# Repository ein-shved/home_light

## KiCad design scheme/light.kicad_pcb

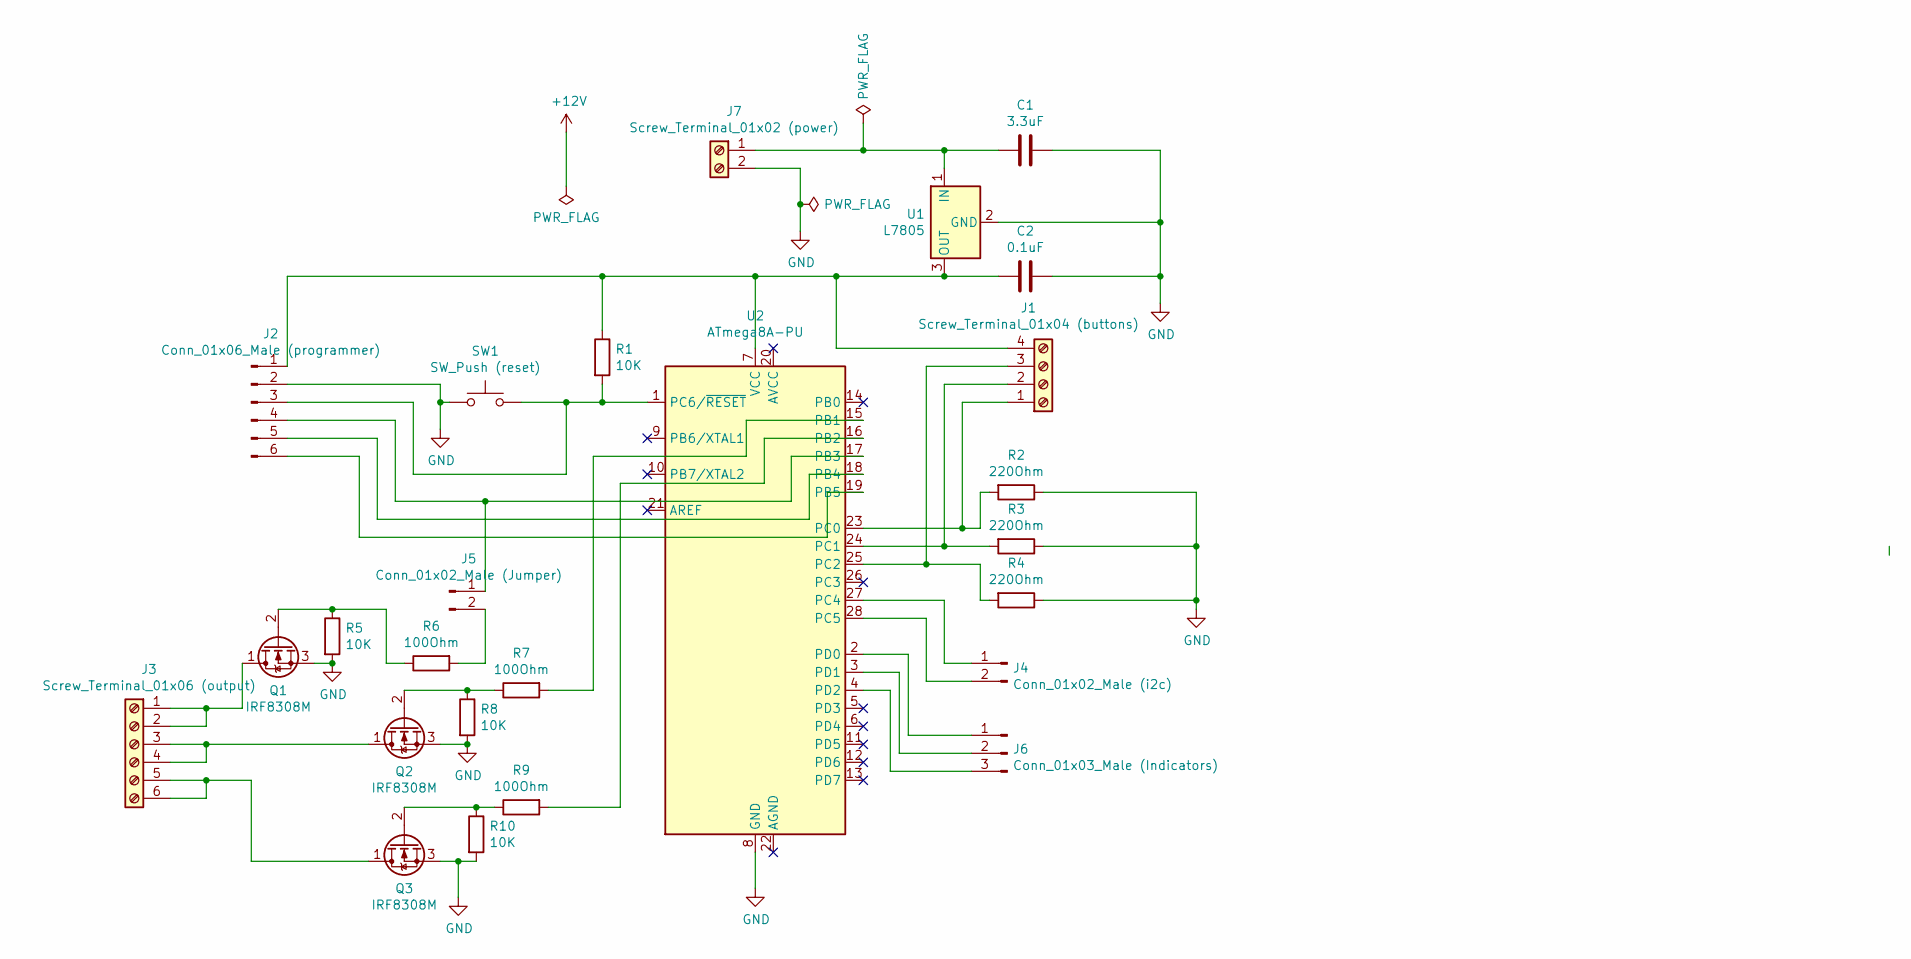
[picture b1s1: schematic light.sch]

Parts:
C1: 3.3uF; C_Disc_D5.1mm_W3.2mm_P5.00mm
C2: 0.1uF; C_Disc_D5.1mm_W3.2mm_P5.00mm
J1: Screw_Terminal_01x04 (buttons); TerminalBlock_Phoenix_MKDS-1,5-4-5.08_1x04_P5.08mm_Horizont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
J2: Conn_01x06_Male (programmer); PinHeader_1x06_P2.54mm_Vertical
J3: Screw_Terminal_01x06 (output); TerminalBlock_Phoenix_MKDS-1,5-6-5.08_1x06_P5.08mm_Horizont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
J4: Conn_01x02_Male (i2c); PinHeader_1x02_P2.54mm_Vertical
J5: Conn_01x02_Male (Jumper); PinHeader_1x02_P2.54mm_Vertical
J6: Conn_01x03_Male (Indicators); PinHeader_1x03_P2.54mm_Vertical
J7: Screw_Terminal_01x02 (power); TerminalBlock_Phoenix_MKDS-1,5-2_1x02_P5.00mm_Horizontal
Q1, Q2, Q3: IRF8308M; IRF840
R1, R5, R8, R10: 10K; R_Axial_DIN0207_L6.3mm_D2.5mm_P7.62mm_Horizontal
R2, R3, R4: 220Ohm; R_Axial_DIN0207_L6.3mm_D2.5mm_P7.62mm_Horizontal
R6, R7, R9: 100Ohm; R_Axial_DIN0207_L6.3mm_D2.5mm_P7.62mm_Horizontal
SW1: SW_Push (reset); SW_PUSH_6mm
U1: L7805; TO-220-3_Vertical
U2: ATmega8A-PU; DIP-28_W7.62mm

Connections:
GND: C1.1, C2.1, J2.2, J7.2, Q1.3 (S), Q2.3 (S), Q3.3 (S), R2.1, R3.1, R4.1, R5.2, R8.2, R10.2, SW1.1, U1.2 (GND), U2.8 (GND)
unnamed: C1.2, J7.1, U1.1 (IN)
unnamed: C2.2, J1.4, J2.1, R1.1, U1.3 (OUT), U2.7 (VCC)
unnamed: J1.1, R2.2, U2.23 (PC0)
unnamed: J1.2, R3.2, U2.24 (PC1)
unnamed: J1.3, R4.2, U2.25 (PC2)
unnamed: J2.3, R1.2, SW1.2, U2.1 (PC6/~RESET)
unnamed: J2.4, J5.1, U2.17 (PB3)
unnamed: J2.5, U2.18 (PB4)
unnamed: J2.6, U2.19 (PB5)
unnamed: J3.1, J3.2, Q1.1 (D)
unnamed: J3.3, J3.4, Q2.1 (D)
unnamed: J3.5, J3.6, Q3.1 (D)
unnamed: J4.1, U2.27 (PC4)
unnamed: J4.2, U2.28 (PC5)
unnamed: J5.2, R6.2
unnamed: J6.1, U2.2 (PD0)
unnamed: J6.2, U2.3 (PD1)
unnamed: J6.3, U2.4 (PD2)
unnamed: Q1.2 (G), R5.1, R6.1
unnamed: Q2.2 (G), R7.1, R8.1
unnamed: Q3.2 (G), R9.1, R10.1
unnamed: R7.2, U2.15 (PB1)
unnamed: R9.2, U2.16 (PB2)

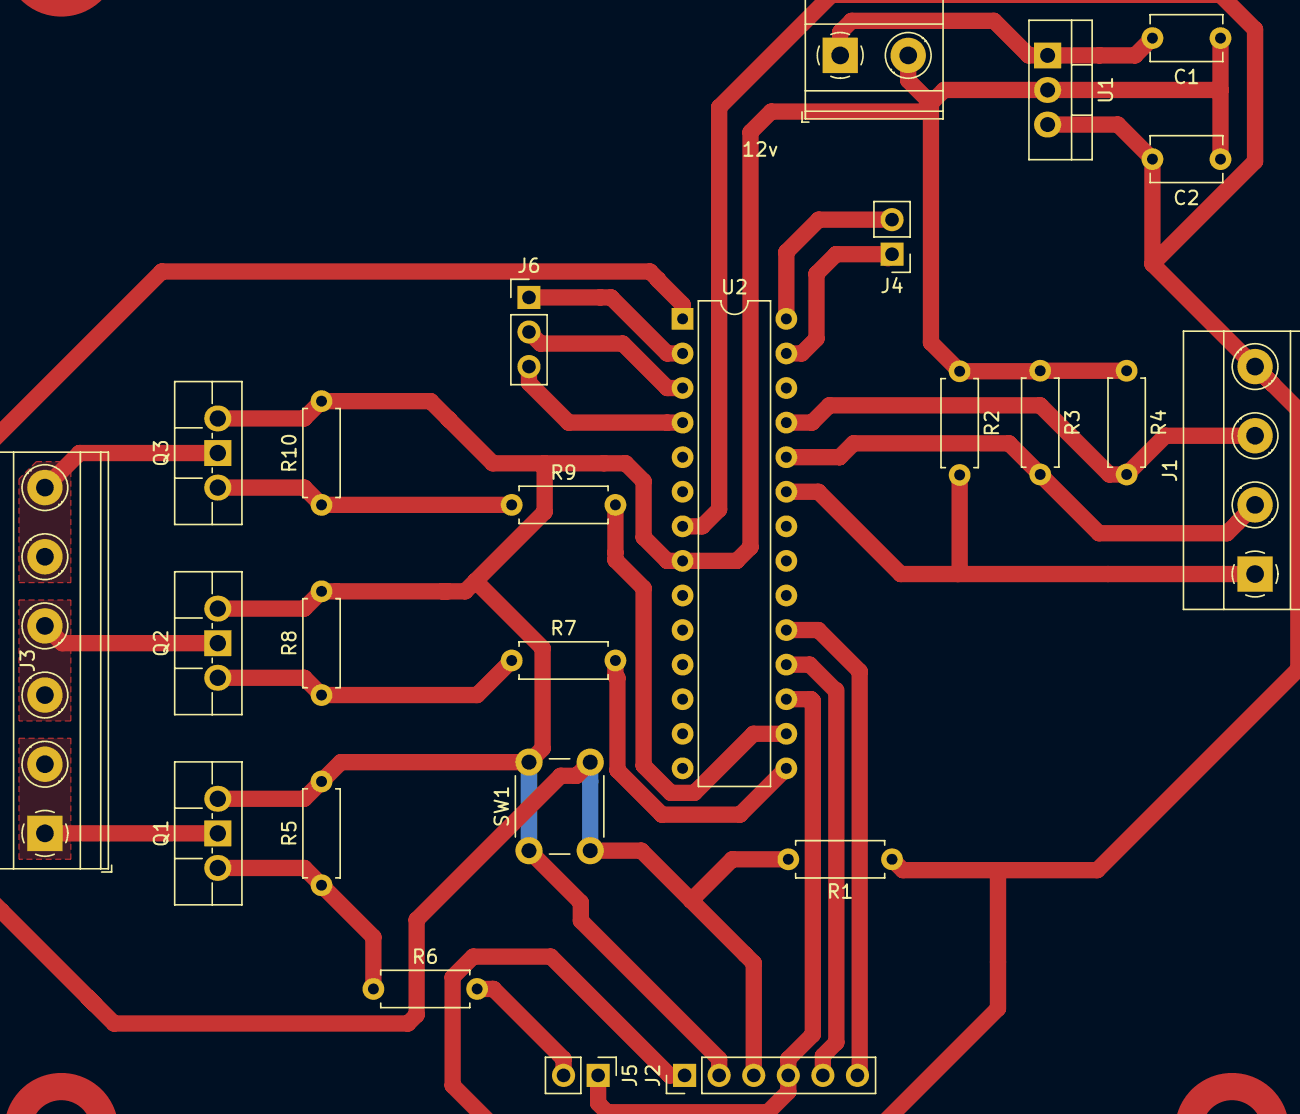
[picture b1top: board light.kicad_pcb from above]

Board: 2 copper layers, 25 parts (0 on the bottom side), 24 nets.

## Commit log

2019-06-29 First commit
    This is first version of home light controller, based on atmega8.
2019-06-29 Final version
    Device now have 8 pairs of buttons and light outputs and all 3 PWMs
    outputs. PWMs connected to first 3 buttons.
2019-07-11 Improve program: involve pwm control with buttons
2019-07-13 pwm_control: fix bugs, update defaults
2019-07-21 Scheme: implement printable trace scheme
2019-07-21 labels: fix power screw terminal orientation
2019-07-22 pcb: prepare onpage 2x2 pcb layouts
2019-07-22 program: output light state to port C
2019-07-24 scheme: change routes widths
    And avoid between pins routes
2019-07-31 scheme: Get rid of second layer
2019-08-05 pwm: fix output pins sequence
2019-08-07 cheme: add marks layer
